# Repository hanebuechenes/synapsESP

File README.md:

# synapsESP – Eurorack ESP32 Control Module

synapsESP ist ein quelloffenes Eurorack-Modul auf Basis des ESP32-Microcontrollers, entwickelt für die flexible Steuerung, Generierung und Verarbeitung von Audio- und CV-Signalen in einem Eurorack-Synthesizer-System.

---

## Features

* ESP32 Core: Leistungsstarke Steuerung für digitale Generierung, DSP und Schnittstellen.
* Display & UI-Integration: Schnittstellen für Displays (z. B. ILI9341 Touch-Display) sowie dedizierte UI-Bedienelemente.
* CV & Audio I/O: Ein- und Ausgänge zur Handhabung von Steuerspannungen (CV) und Audiosignalen im Eurorack-Standard.
* Spannungsversorgung: Standard Eurorack Power-Anschluss mit integrierter Schutzbeschaltung.

---

## Projektstruktur

synapsESP/
├── audio.kicad_sch        # Schaltplan: Audio I/O
├── cv.kicad_sch           # Schaltplan: CV-Eingänge/Ausgänge
├── io.kicad_sch           # Schaltplan: Allgemeine E/A & Peripherie
├── power.kicad_sch        # Schaltplan: Stromversorgung & Schutz
├── ui.kicad_sch           # Schaltplan: Benutzeroberfläche / Bedienelemente
├── esp32.kicad_pcb        # KiCad PCB Layout
├── esp32.kicad_pro        # KiCad Hauptprojekt
├── Display_ILI9341.*      # Symbol- & Footprint-Bibliotheken für das Display
└── .gitignore             # Git-Ausschlusskriterien für temporäre KiCad-Dateien

---

## Hardware & Design

Das Modul wurde in KiCad strukturiert und modular aufgebaut. Es teilt die unterschiedlichen Blöcke (Audio, CV, UI, Power) in übersichtliche Schaltplan-Hierarchien auf.

### Voraussetzungen / Design-Tools

* KiCad (Empfohlen: v7 oder neuer)
* Passende Bibliotheken für Gehäuse-/Panel-Abmessungen und Spezialkomponenten (z. B. Display-Module)

---

## Inbetriebnahme & Git

Um das Projekt lokal zu klonen:

git clone https://github.com/hanebuechenes/synapsESP.git

Öffne anschließend die Datei esp32.kicad_pro in KiCad, um den Schaltplan zu lesen oder das PCB-Layout anzupassen.

---

## Lizenz

Dieses Projekt ist unter der CERN Open Hardware Licence / MIT License veröffentlicht (frei zur persönlichen Nutzung und Modifikation).

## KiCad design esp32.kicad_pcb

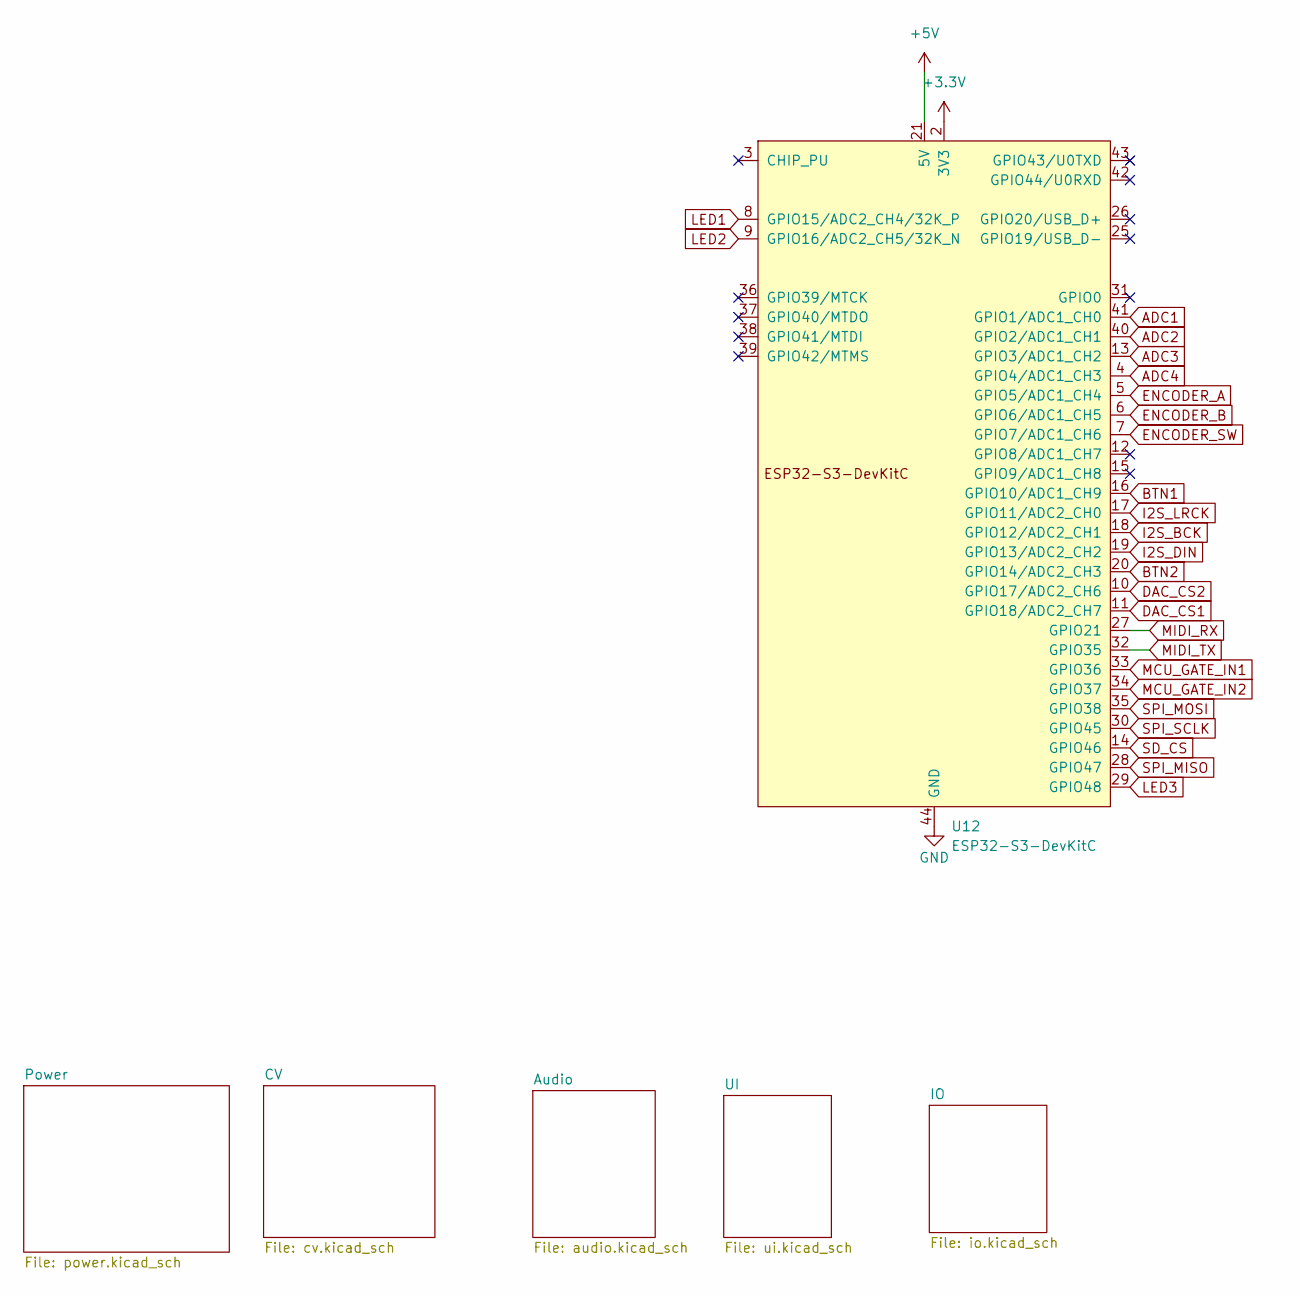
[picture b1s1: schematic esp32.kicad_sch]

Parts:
U12: ESP32-S3-DevKitC

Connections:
+3.3V: U12.1 (3V3), U12.2 (3V3); also elsewhere on the board
+5V: U12.21 (5V); also elsewhere on the board
ADC1: U12.41 (GPIO1/ADC1_CH0); also elsewhere on the board
ADC2: U12.40 (GPIO2/ADC1_CH1); also elsewhere on the board
ADC3: U12.13 (GPIO3/ADC1_CH2); also elsewhere on the board
ADC4: U12.4 (GPIO4/ADC1_CH3); also elsewhere on the board
BTN1: U12.16 (GPIO10/ADC1_CH9); also elsewhere on the board
BTN2: U12.20 (GPIO14/ADC2_CH3); also elsewhere on the board
DAC_CS1: U12.11 (GPIO18/ADC2_CH7); also elsewhere on the board
DAC_CS2: U12.10 (GPIO17/ADC2_CH6); also elsewhere on the board
ENCODER_A: U12.5 (GPIO5/ADC1_CH4); also elsewhere on the board
ENCODER_B: U12.6 (GPIO6/ADC1_CH5); also elsewhere on the board
ENCODER_SW: U12.7 (GPIO7/ADC1_CH6); also elsewhere on the board
GND: U12.22 (GND), U12.23 (GND), U12.24 (GND), U12.44 (GND); also elsewhere on the board
I2S_BCK: U12.18 (GPIO12/ADC2_CH1); also elsewhere on the board
I2S_DIN: U12.19 (GPIO13/ADC2_CH2); also elsewhere on the board
I2S_LRCK: U12.17 (GPIO11/ADC2_CH0); also elsewhere on the board
LED1: U12.8 (GPIO15/ADC2_CH4/32K_P); also elsewhere on the board
LED2: U12.9 (GPIO16/ADC2_CH5/32K_N); also elsewhere on the board
LED3: U12.29 (GPIO48); also elsewhere on the board
MCU_GATE_IN1: U12.33 (GPIO36); also elsewhere on the board
MCU_GATE_IN2: U12.34 (GPIO37); also elsewhere on the board
MIDI_RX: U12.27 (GPIO21); also elsewhere on the board
MIDI_TX: U12.32 (GPIO35); also elsewhere on the board
SD_CS: U12.14 (GPIO46); also elsewhere on the board
SPI_MISO: U12.28 (GPIO47); also elsewhere on the board
SPI_MOSI: U12.35 (GPIO38); also elsewhere on the board
SPI_SCLK: U12.30 (GPIO45); also elsewhere on the board

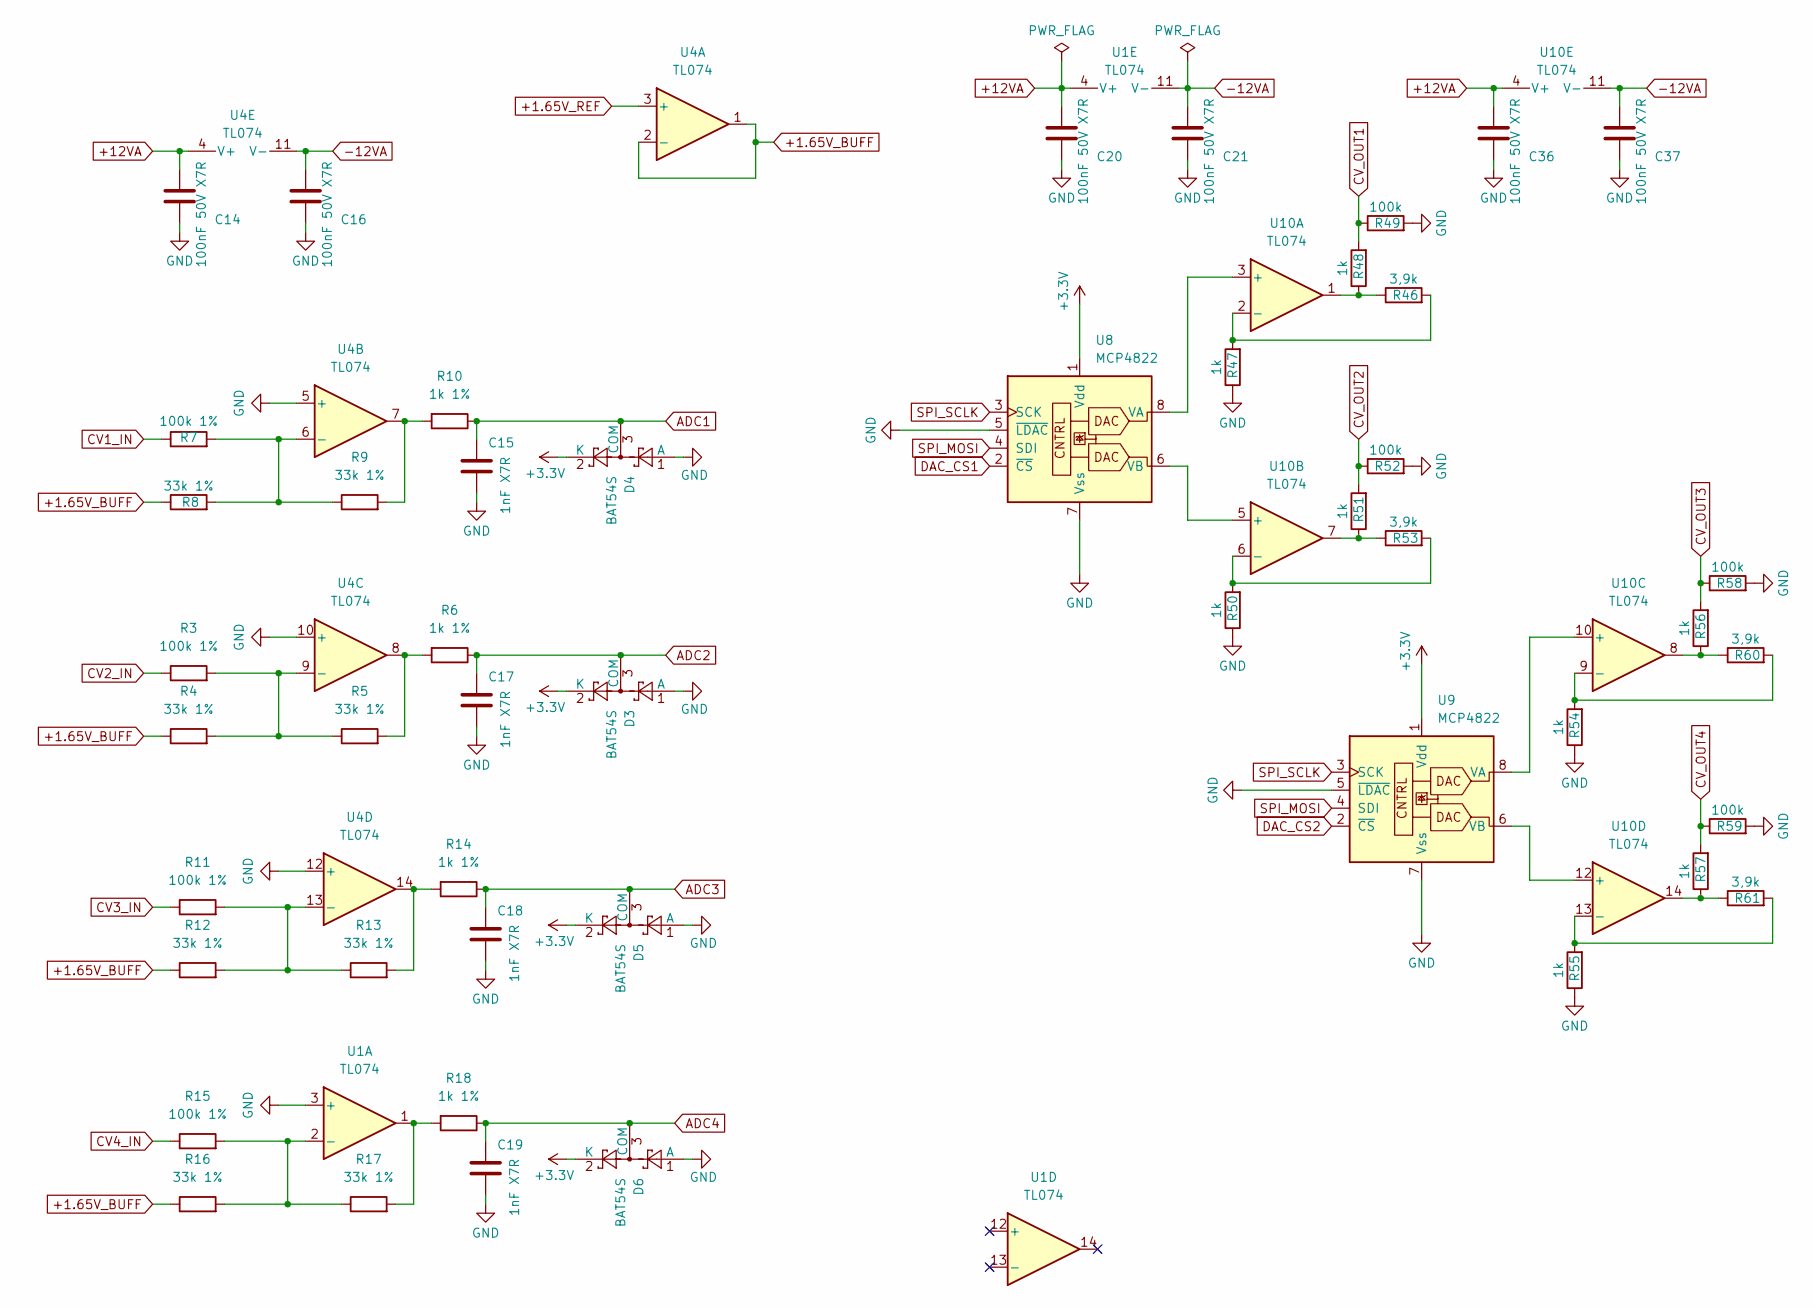
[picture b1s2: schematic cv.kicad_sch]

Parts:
C14, C16, C20, C21, C36, C37: 100nF 50V X7R; C_0805_2012Metric_Pad1.18x1.45mm_HandSolder
C15, C17, C18, C19: 1nF X7R; C_0603_1608Metric_Pad1.08x0.95mm_HandSolder
D3, D4, D5, D6: BAT54S; SOT-23
R3, R7, R11, R15: 100k 1%; R_0603_1608Metric_Pad0.98x0.95mm_HandSolder
R4, R5, R8, R9, R12, R13, R16, R17: 33k 1%; R_0603_1608Metric_Pad0.98x0.95mm_HandSolder
R6, R10, R14, R18: 1k 1%; R_0603_1608Metric_Pad0.98x0.95mm_HandSolder
R46, R53, R60, R61: 3,9k; R_0603_1608Metric_Pad0.98x0.95mm_HandSolder
R47, R48, R50, R51, R54, R55, R56, R57: 1k; R_0603_1608Metric_Pad0.98x0.95mm_HandSolder
R49, R52, R58, R59: 100k; R_0603_1608Metric_Pad0.98x0.95mm_HandSolder
U1, U4, U10: TL074; SOIC-14_3.9x8.7mm_P1.27mm
U8, U9: MCP4822; SOIC-8_3.9x4.9mm_P1.27mm

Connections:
+1.65V_BUFF: R4.1, R8.1, R12.1, R16.1, U4.1, U4.2 (-); also elsewhere on the board
+1.65V_REF: U4.3 (+); also elsewhere on the board
+3.3V: D3.2 (K), D4.2 (K), D5.2 (K), D6.2 (K), U8.1 (Vdd), U9.1 (Vdd); also elsewhere on the board
+12VA: C14.1, C20.1, C36.1, U1.4 (V+), U4.4 (V+), U10.4 (V+); also elsewhere on the board
-12VA: C16.1, C21.1, C37.1, U1.11 (V-), U4.11 (V-), U10.11 (V-); also elsewhere on the board
ADC1: C15.1, D4.3 (COM), R10.1; also elsewhere on the board
ADC2: C17.1, D3.3 (COM), R6.1; also elsewhere on the board
ADC3: C18.1, D5.3 (COM), R14.1; also elsewhere on the board
ADC4: C19.1, D6.3 (COM), R18.1; also elsewhere on the board
CV1_IN: R7.1; also elsewhere on the board
CV2_IN: R3.1; also elsewhere on the board
CV3_IN: R11.1; also elsewhere on the board
CV4_IN: R15.1; also elsewhere on the board
CV_OUT1: R48.2, R49.1
CV_OUT2: R51.2, R52.1
CV_OUT3: R56.2, R58.1
CV_OUT4: R57.2, R59.1
DAC_CS1: U8.2 (~CS); also elsewhere on the board
DAC_CS2: U9.2 (~CS); also elsewhere on the board
GND: C14.2, C15.2, C16.2, C17.2, C18.2, C19.2, C20.2, C21.2, C36.2, C37.2, D3.1 (A), D4.1 (A), D5.1 (A), D6.1 (A), R47.1, R49.2, R50.1, R52.2, R54.1, R55.1, R58.2, R59.2, U1.3 (+), U4.5 (+), U4.10 (+), U4.12 (+), U8.5 (~LDAC), U8.7 (Vss), U9.5 (~LDAC), U9.7 (Vss); also elsewhere on the board
unnamed: R5.2, R6.2, U4.8
unnamed: R9.2, R10.2, U4.7
unnamed: R13.2, R14.2, U4.14
unnamed: R17.2, R18.2, U1.1
unnamed: R46.1, R48.1, U10.1
unnamed: R51.1, R53.1, U10.7
unnamed: R56.1, R60.1, U10.8
unnamed: R57.1, R61.1, U10.14
unnamed: R15.2, R16.2, R17.1, U1.2 (-)
unnamed: R7.2, R8.2, R9.1, U4.6 (-)
unnamed: R3.2, R4.2, R5.1, U4.9 (-)
unnamed: R11.2, R12.2, R13.1, U4.13 (-)
unnamed: U8.8 (VA), U10.3 (+)
unnamed: R46.2, R47.2, U10.2 (-)
unnamed: U8.6 (VB), U10.5 (+)
unnamed: R50.2, R53.2, U10.6 (-)
unnamed: U9.8 (VA), U10.10 (+)
unnamed: R54.2, R60.2, U10.9 (-)
unnamed: U9.6 (VB), U10.12 (+)
unnamed: R55.2, R61.2, U10.13 (-)
SPI_MOSI: U8.4 (SDI), U9.4 (SDI); also elsewhere on the board
SPI_SCLK: U8.3 (SCK), U9.3 (SCK); also elsewhere on the board

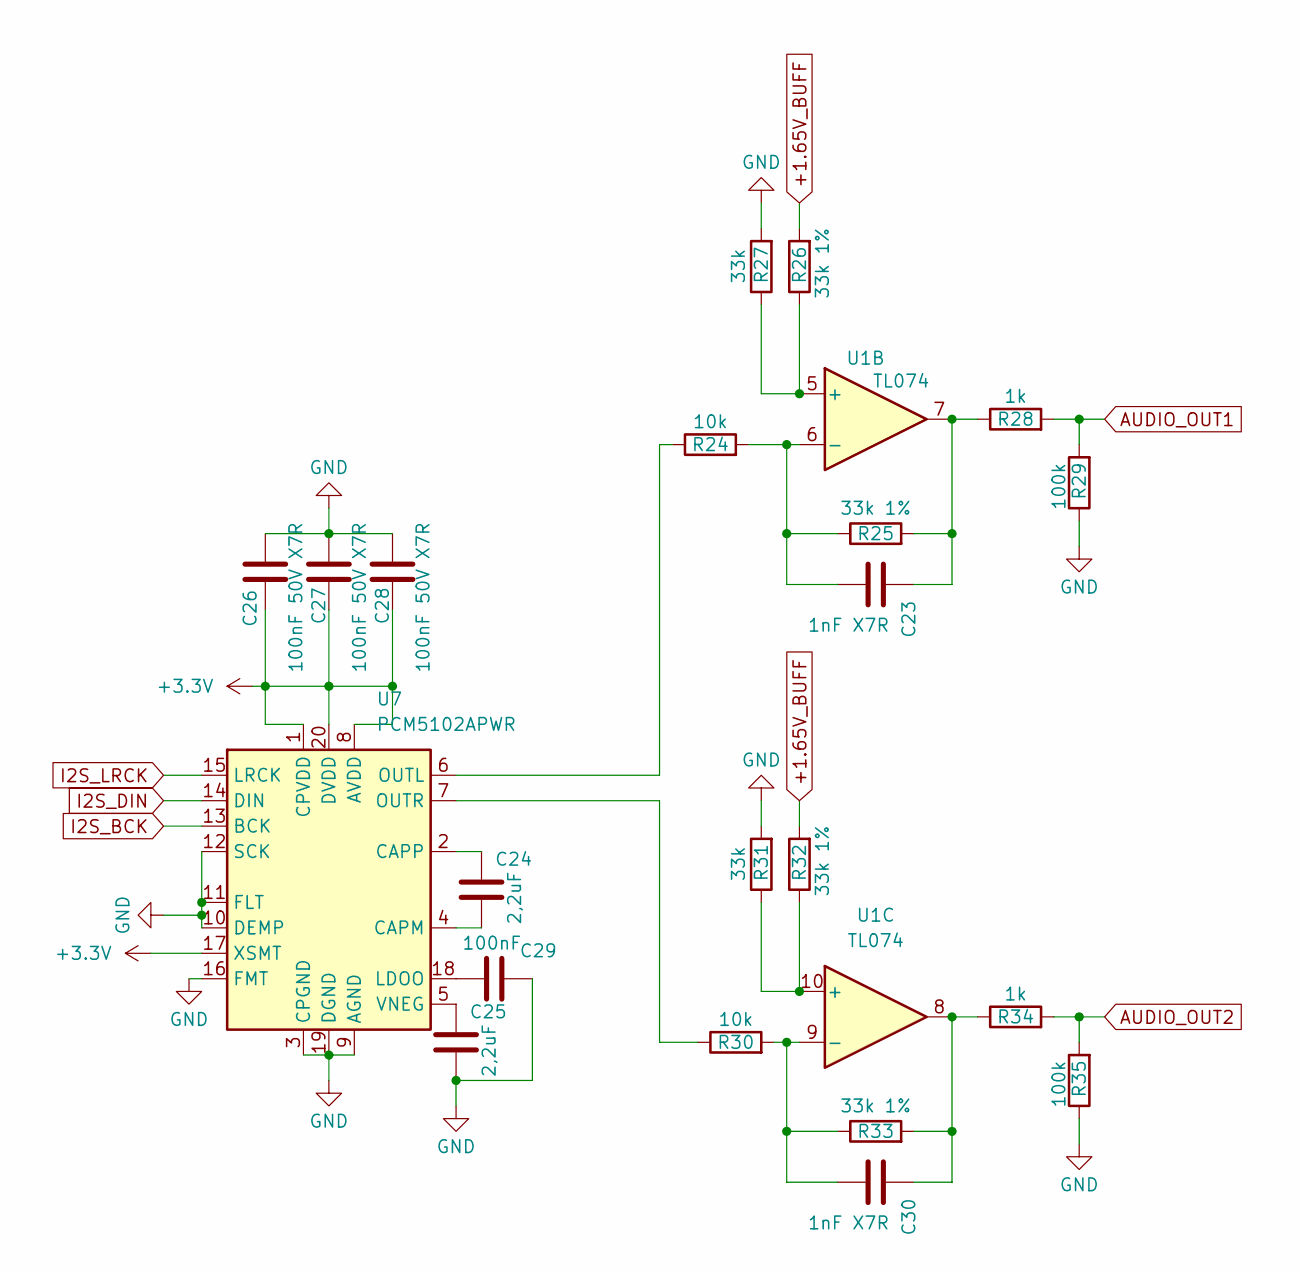
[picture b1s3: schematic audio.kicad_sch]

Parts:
C23, C30: 1nF X7R; C_0603_1608Metric_Pad1.08x0.95mm_HandSolder
C24, C25: 2,2uF; C_0805_2012Metric_Pad1.18x1.45mm_HandSolder
C26, C27, C28: 100nF 50V X7R; C_0805_2012Metric_Pad1.18x1.45mm_HandSolder
C29: 100nF; C_0805_2012Metric_Pad1.18x1.45mm_HandSolder
R24, R30: 10k; R_0603_1608Metric_Pad0.98x0.95mm_HandSolder
R25, R26, R32, R33: 33k 1%; R_0603_1608Metric_Pad0.98x0.95mm_HandSolder
R27, R31: 33k; R_0603_1608Metric_Pad0.98x0.95mm_HandSolder
R28, R34: 1k; R_0603_1608Metric_Pad0.98x0.95mm_HandSolder
R29, R35: 100k; R_0603_1608Metric_Pad0.98x0.95mm_HandSolder
U1: TL074; SOIC-14_3.9x8.7mm_P1.27mm
U7: PCM5102APWR; TSSOP-20_4.4x6.5mm_P0.65mm

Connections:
+1.65V_BUFF: R26.2, R32.2; also elsewhere on the board
+3.3V: C26.2, C27.2, C28.2, U7.1 (CPVDD), U7.8 (AVDD), U7.17 (XSMT), U7.20 (DVDD); also elsewhere on the board
AUDIO_OUT1: R28.2, R29.2; also elsewhere on the board
AUDIO_OUT2: R34.2, R35.2; also elsewhere on the board
GND: C25.2, C26.1, C27.1, C28.1, C29.2, R27.2, R29.1, R31.2, R35.1, U7.3 (CPGND), U7.9 (AGND), U7.10 (DEMP), U7.11 (FLT), U7.12 (SCK), U7.16 (FMT), U7.19 (DGND); also elsewhere on the board
I2S_BCK: U7.13 (BCK); also elsewhere on the board
I2S_DIN: U7.14 (DIN); also elsewhere on the board
I2S_LRCK: U7.15 (LRCK); also elsewhere on the board
unnamed: C23.1, R25.2, R28.1, U1.7
unnamed: C30.1, R33.2, R34.1, U1.8
unnamed: R26.1, R27.1, U1.5 (+)
unnamed: C23.2, R24.2, R25.1, U1.6 (-)
unnamed: R31.1, R32.1, U1.10 (+)
unnamed: C30.2, R30.2, R33.1, U1.9 (-)
unnamed: C24.2, U7.4 (CAPM)
unnamed: C24.1, U7.2 (CAPP)
unnamed: C29.1, U7.18 (LDOO)
unnamed: R24.1, U7.6 (OUTL)
unnamed: R30.1, U7.7 (OUTR)
unnamed: C25.1, U7.5 (VNEG)

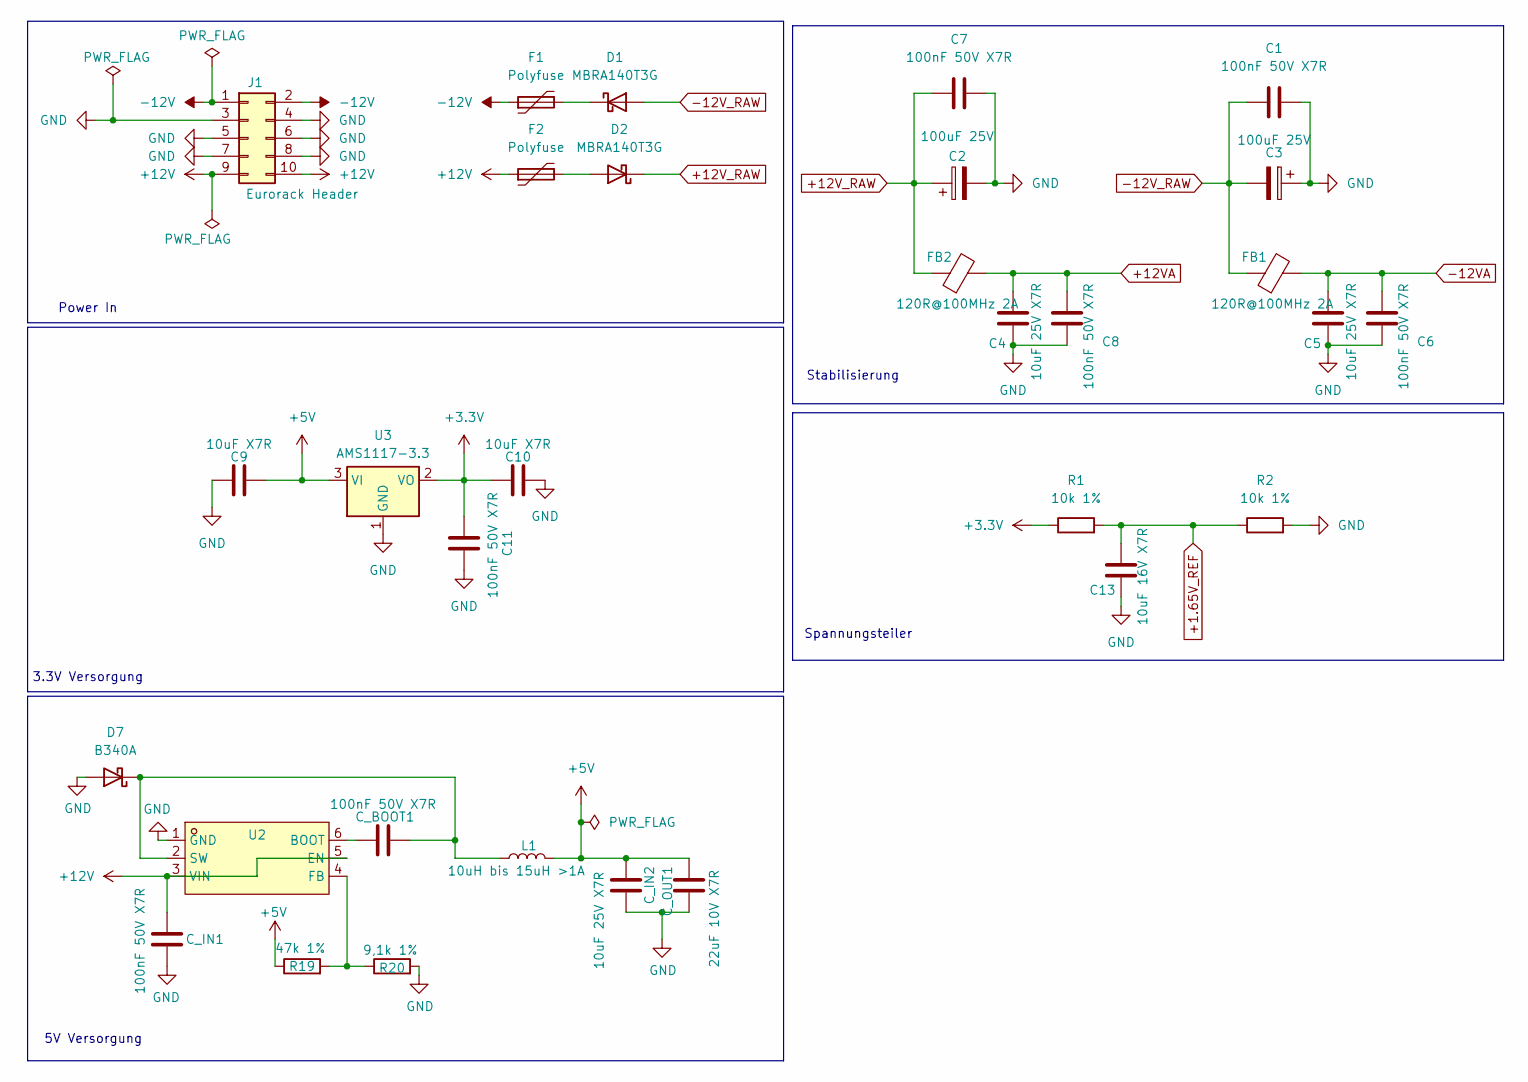
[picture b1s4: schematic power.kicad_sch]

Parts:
C1, C6, C7, C8, C11: 100nF 50V X7R; C_0805_2012Metric_Pad1.18x1.45mm_HandSolder
C2, C3: 100uF 25V; CP_Elec_6.3x7.7
C4, C5: 10uF 25V X7R; C_0805_2012Metric_Pad1.18x1.45mm_HandSolder
C9, C10: 10uF X7R; C_0805_2012Metric_Pad1.18x1.45mm_HandSolder
C13: 10uF 16V X7R; C_0805_2012Metric_Pad1.18x1.45mm_HandSolder
C_BOOT1: 100nF 50V X7R; C_0603_1608Metric_Pad1.08x0.95mm_HandSolder
C_IN1: 100nF 50V X7R; C_0603_1608Metric_Pad1.08x0.95mm_HandSolder
C_IN2: 10uF 25V X7R; C_1206_3216Metric_Pad1.33x1.80mm_HandSolder
C_OUT1: 22uF 10V X7R; C_0805_2012Metric_Pad1.18x1.45mm_HandSolder
D1, D2: MBRA140T3G; D_SMA-SMB_Universal_Handsoldering
D7: B340A; D_SMC
F1, F2: Polyfuse; Fuse_1210_3225Metric
FB1, FB2: 120R@100MHz 2A; L_0603_1608Metric_Pad1.05x0.95mm_HandSolder
J1: Eurorack Header; PinHeader_2x05_P2.54mm_Vertical
L1: 10uH bis 15uH >1A; L_Coilcraft_XxL4030
R1, R2: 10k 1%; R_0603_1608Metric_Pad0.98x0.95mm_HandSolder
R19: 47k 1%; R_0603_1608Metric_Pad0.98x0.95mm_HandSolder
R20: 9,1k 1%; R_0603_1608Metric_Pad0.98x0.95mm_HandSolder
U2: TPS54302DDCR_C311983; SOT-23-6_L2.9-W1.6-P0.95-LS2.8-BL; MPN TPS54302DDCR; LCSC Part C311983
U3: AMS1117-3.3; SOT-223-3_TabPin2

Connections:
+1.65V_REF: C13.1, R1.2, R2.1; also elsewhere on the board
+3.3V: C10.2, C11.1, R1.1, U3.2 (VO); also elsewhere on the board
+5V: C9.1, C_IN2.1, C_OUT1.1, L1.2, R19.1, U3.3 (VI); also elsewhere on the board
+12V: C_IN1.1, F2.1, J1.9, J1.10, U2.3 (VIN), U2.5 (EN)
+12VA: C4.1, C8.1, FB2.2; also elsewhere on the board
+12V_RAW: C2.1, C7.1, D2.1 (K), FB2.1
-12V: F1.1, J1.1, J1.2
-12VA: C5.1, C6.1, FB1.2; also elsewhere on the board
-12V_RAW: C1.1, C3.2, D1.2 (A), FB1.1
GND: C1.2, C2.2, C3.1, C4.2, C5.2, C6.2, C7.2, C8.2, C9.2, C10.1, C11.2, C13.2, C_IN1.2, C_IN2.2, C_OUT1.2, D7.2 (A), J1.3, J1.4, J1.5, J1.6, J1.7, J1.8, R2.2, R20.2, U2.1 (GND), U3.1 (GND); also elsewhere on the board
unnamed: D1.1 (K), F1.2
unnamed: D2.2 (A), F2.2
unnamed: C_BOOT1.2, D7.1 (K), L1.1, U2.2 (SW)
unnamed: C_BOOT1.1, U2.6 (BOOT)
unnamed: R19.2, R20.1, U2.4 (FB)

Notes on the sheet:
Stabilisierung
5V Versorgung
Spannungsteiler
3.3V Versorgung
Power In

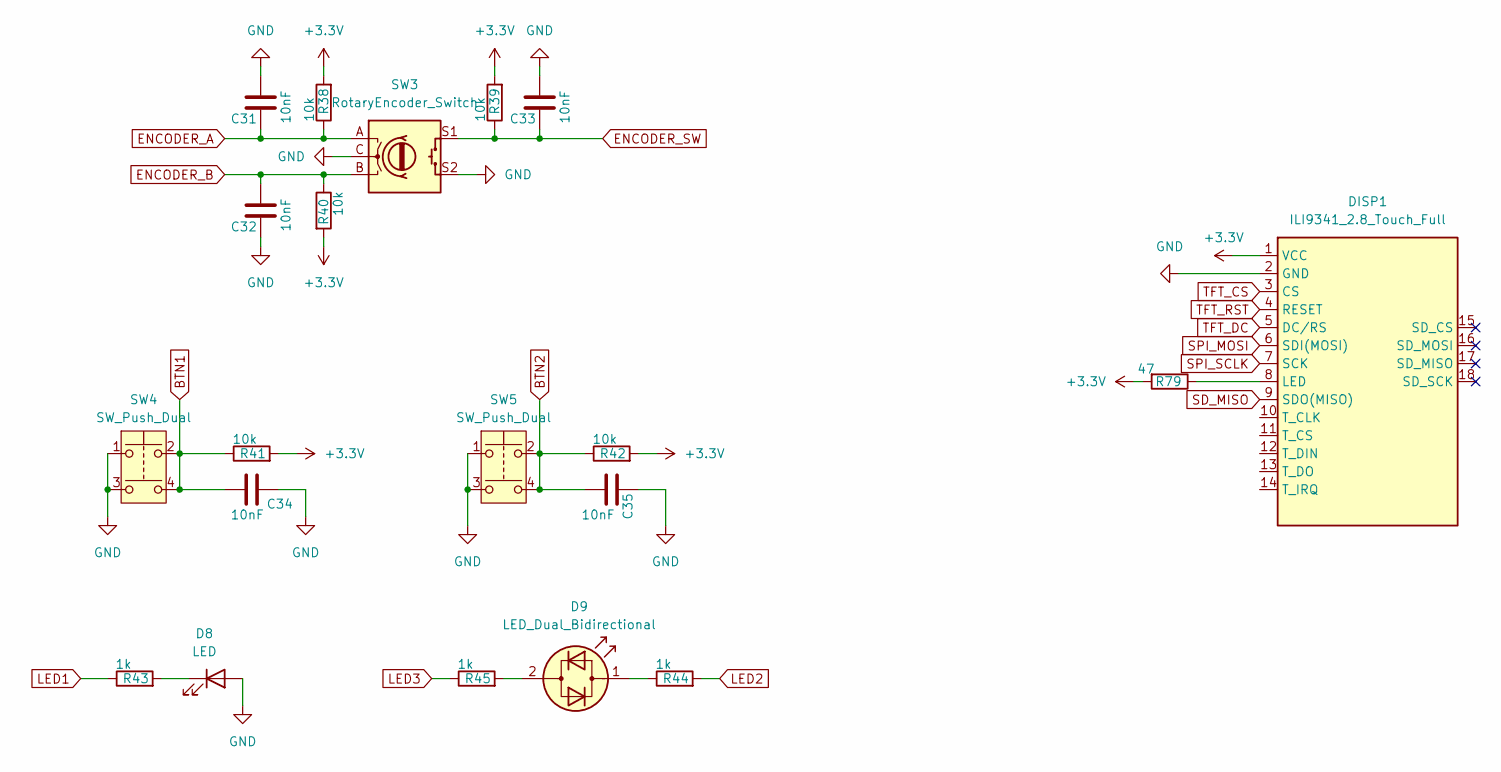
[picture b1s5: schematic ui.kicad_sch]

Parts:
C31, C32, C33, C34, C35: 10nF; C_0603_1608Metric_Pad1.08x0.95mm_HandSolder
D8: LED; LED_D3.0mm
D9: LED_Dual_Bidirectional; LED_D3.0mm
DISP1: ILI9341_2.8_Touch_Full; ILI9341-2.8
R38, R39, R40, R41, R42: 10k; R_0603_1608Metric_Pad0.98x0.95mm_HandSolder
R43, R44, R45: 1k; R_0603_1608Metric_Pad0.98x0.95mm_HandSolder
R79: 47; R_0603_1608Metric_Pad0.98x0.95mm_HandSolder
SW3: RotaryEncoder_Switch; RotaryEncoder_Alps_EC11E-Switch_Vertical_H20mm
SW4, SW5: SW_Push_Dual; SW_PUSH_6mm

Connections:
+3.3V: DISP1.1 (VCC), R38.2, R39.2, R40.2, R41.2, R42.2, R79.2; also elsewhere on the board
BTN1: C34.2, R41.1, SW4.2, SW4.4; also elsewhere on the board
BTN2: C35.1, R42.1, SW5.2, SW5.4; also elsewhere on the board
ENCODER_A: C31.2, R38.1, SW3.A; also elsewhere on the board
ENCODER_B: C32.1, R40.1, SW3.B; also elsewhere on the board
ENCODER_SW: C33.2, R39.1, SW3.S1; also elsewhere on the board
GND: C31.1, C32.2, C33.1, C34.1, C35.2, D8.2 (A), DISP1.2 (GND), SW3.C, SW3.S2, SW4.1, SW4.3, SW5.1, SW5.3; also elsewhere on the board
LED1: R43.1; also elsewhere on the board
LED2: R44.2; also elsewhere on the board
LED3: R45.1; also elsewhere on the board
unnamed: D8.1 (K), R43.2
unnamed: D9.2 (AK), R45.2
unnamed: D9.1 (KA), R44.1
unnamed: DISP1.8 (LED), R79.1
SD_MISO: DISP1.9 (SDO(MISO))
SPI_MOSI: DISP1.6 (SDI(MOSI)); also elsewhere on the board
SPI_SCLK: DISP1.7 (SCK); also elsewhere on the board
TFT_CS: DISP1.3 (CS)
TFT_DC: DISP1.5 (DC/RS)
TFT_RST: DISP1.4 (RESET)

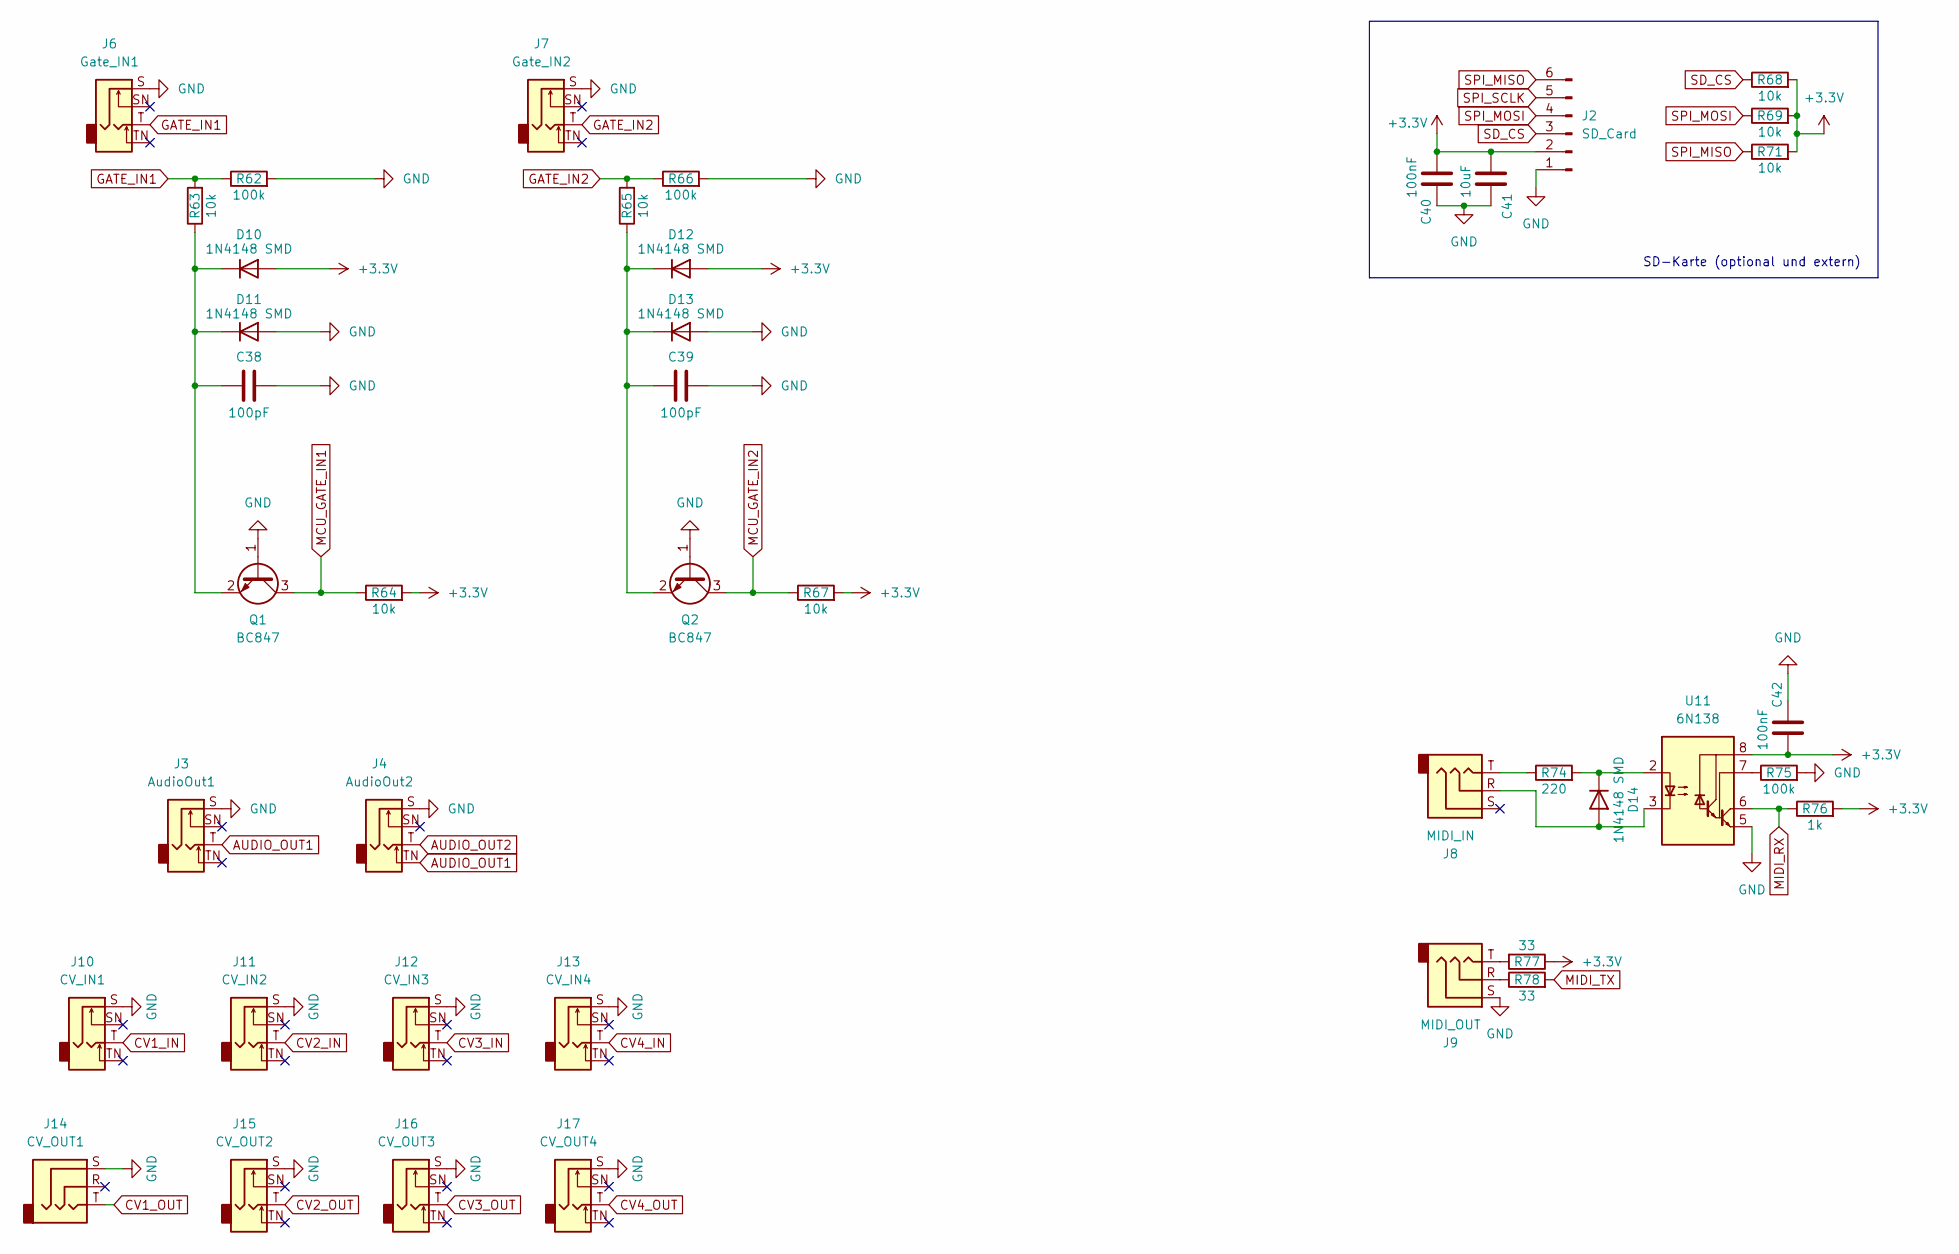
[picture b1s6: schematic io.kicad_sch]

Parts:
C38, C39: 100pF; C_0603_1608Metric_Pad1.08x0.95mm_HandSolder
C40, C42: 100nF; C_0805_2012Metric_Pad1.18x1.45mm_HandSolder
C41: 10uF; C_0805_2012Metric_Pad1.18x1.45mm_HandSolder
D10, D11, D12, D13, D14: 1N4148 SMD; D_SOD-123
J2: SD_Card; PinHeader_1x06_P2.54mm_Vertical
J3: AudioOut1; PJ301M-12-NoHole
J4: AudioOut2; PJ301M-12-NoHole
J6: Gate_IN1; PJ301M-12-NoHole
J7: Gate_IN2; PJ301M-12-NoHole
J8: MIDI_IN; PJ366ST
J9: MIDI_OUT; PJ366ST
J10: CV_IN1; PJ301M-12-NoHole
J11: CV_IN2; PJ301M-12-NoHole
J12: CV_IN3; PJ301M-12-NoHole
J13: CV_IN4; PJ301M-12-NoHole
J14: CV_OUT1; PJ366ST
J15: CV_OUT2; PJ301M-12-NoHole
J16: CV_OUT3; PJ301M-12-NoHole
J17: CV_OUT4; PJ301M-12-NoHole
Q1, Q2: BC847; SOT-23
R62, R66, R75: 100k; R_0603_1608Metric_Pad0.98x0.95mm_HandSolder
R63, R64, R65, R67, R68, R69, R71: 10k; R_0603_1608Metric_Pad0.98x0.95mm_HandSolder
R74: 220; R_0603_1608Metric_Pad0.98x0.95mm_HandSolder
R76: 1k; R_0603_1608Metric_Pad0.98x0.95mm_HandSolder
R77, R78: 33; R_0603_1608Metric_Pad0.98x0.95mm_HandSolder
U11: 6N138; SOIC-8_3.9x4.9mm_P1.27mm

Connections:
+3.3V: C40.1, C41.1, C42.1, D10.2 (A), D12.2 (A), J2.2, R64.2, R67.2, R68.2, R69.2, R71.2, R76.2, R77.1, U11.8 (VCC); also elsewhere on the board
AUDIO_OUT1: J3.T, J4.TN; also elsewhere on the board
AUDIO_OUT2: J4.T; also elsewhere on the board
CV1_IN: J10.T; also elsewhere on the board
CV1_OUT: J14.T
CV2_IN: J11.T; also elsewhere on the board
CV2_OUT: J15.T
CV3_IN: J12.T; also elsewhere on the board
CV3_OUT: J16.T
CV4_IN: J13.T; also elsewhere on the board
CV4_OUT: J17.T
GATE_IN1: J6.T, R62.1, R63.2
GATE_IN2: J7.T, R65.2, R66.1
GND: C38.2, C39.2, C40.2, C41.2, C42.2, D11.2 (A), D13.2 (A), J2.1, J3.S, J4.S, J6.S, J7.S, J9.S, J10.S, J11.S, J12.S, J13.S, J14.S, J15.S, J16.S, J17.S, Q1.1 (B), Q2.1 (B), R62.2, R66.2, R75.2, U11.5 (GND); also elsewhere on the board
MCU_GATE_IN1: Q1.3 (C), R64.1; also elsewhere on the board
MCU_GATE_IN2: Q2.3 (C), R67.1; also elsewhere on the board
MIDI_RX: R76.1, U11.6 (VO2); also elsewhere on the board
MIDI_TX: R78.2; also elsewhere on the board
unnamed: C38.1, D10.1 (K), D11.1 (K), Q1.2 (E), R63.1
unnamed: C39.1, D12.1 (K), D13.1 (K), Q2.2 (E), R65.1
unnamed: D14.2 (A), J8.R, U11.3 (C2)
unnamed: D14.1 (K), R74.2, U11.2 (C1)
unnamed: J8.T, R74.1
unnamed: J9.R, R78.1
unnamed: J9.T, R77.2
unnamed: R75.1, U11.7 (VO1)
SD_CS: J2.3, R68.1; also elsewhere on the board
SPI_MISO: J2.6, R71.1; also elsewhere on the board
SPI_MOSI: J2.4, R69.1; also elsewhere on the board
SPI_SCLK: J2.5; also elsewhere on the board

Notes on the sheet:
SD-Karte (optional und extern)

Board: 2 copper layers, 166 parts (107 on the bottom side), 97 nets, no tracks yet.
